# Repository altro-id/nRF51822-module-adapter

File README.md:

# nRF51822-module-adapter
This is an adapter to 2.54mm pitch for nRF51822 Module Board

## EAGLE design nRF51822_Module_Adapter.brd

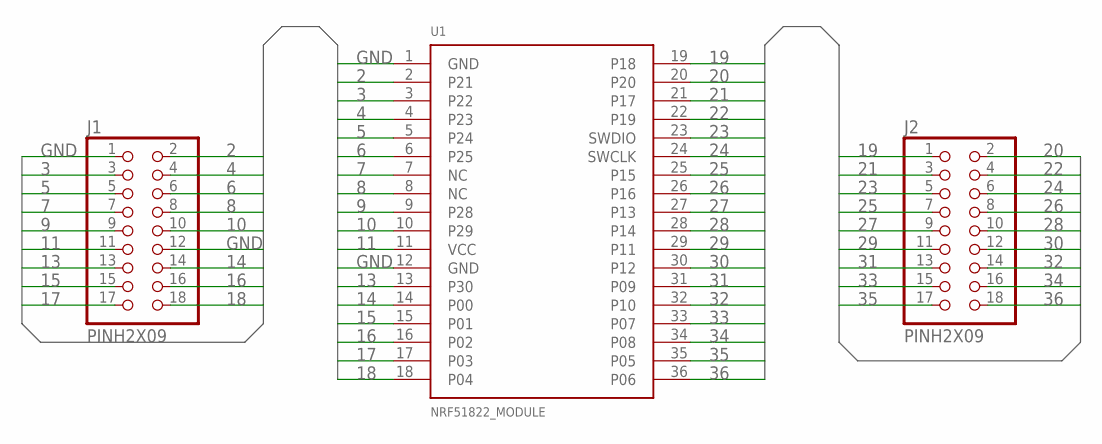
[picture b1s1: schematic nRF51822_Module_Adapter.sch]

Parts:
J1, J2: PINH2X09
U1: NRF51822_MODULE

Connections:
2: J1.2, U1.2 (P21)
3: J1.3, U1.3 (P22)
4: J1.4, U1.4 (P23)
5: J1.5, U1.5 (P24)
6: J1.6, U1.6 (P25)
7: J1.7, U1.7 (NC)
8: J1.8, U1.8 (NC)
9: J1.9, U1.9 (P28)
10: J1.10, U1.10 (P29)
11: J1.11, U1.11 (VCC)
13: J1.13, U1.13 (P30)
14: J1.14, U1.14 (P00)
15: J1.15, U1.15 (P01)
16: J1.16, U1.16 (P02)
17: J1.17, U1.17 (P03)
18: J1.18, U1.18 (P04)
19: J2.1, U1.19 (P18)
20: J2.2, U1.20
21: J2.3, U1.21 (P17)
22: J2.4, U1.22 (P19)
23: J2.5, U1.23 (SWDIO)
24: J2.6, U1.24 (SWCLK)
25: J2.7, U1.25 (P15)
26: J2.8, U1.26 (P16)
27: J2.9, U1.27 (P13)
28: J2.10, U1.28 (P14)
29: J2.11, U1.29 (P11)
30: J2.12, U1.30 (P12)
31: J2.13, U1.31 (P09)
32: J2.14, U1.32 (P10)
33: J2.15, U1.33 (P07)
34: J2.16, U1.34 (P08)
35: J2.17, U1.35 (P05)
36: J2.18, U1.36 (P06)
GND: J1.1, J1.12, U1.1 (GND), U1.12 (GND)

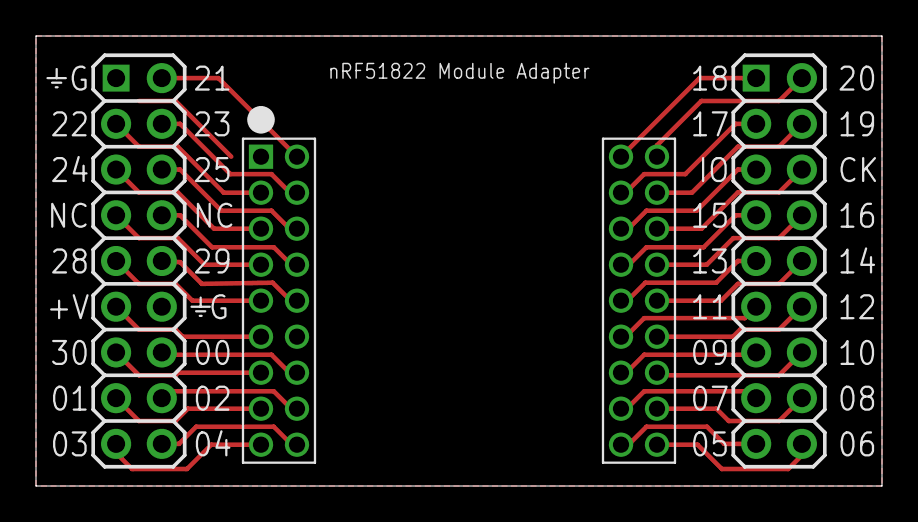
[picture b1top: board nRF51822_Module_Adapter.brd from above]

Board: 2 copper layers, 47.0 x 25.0 mm, 3 parts (0 on the bottom side), 35 nets.

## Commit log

2017-08-10 Added SCH and BRD files
